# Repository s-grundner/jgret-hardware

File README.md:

# jgret-hardware

## Pico VGA Board

| Vorne                        | Hinten                             |
| ---------------------------- | ---------------------------------- |
|  |  |

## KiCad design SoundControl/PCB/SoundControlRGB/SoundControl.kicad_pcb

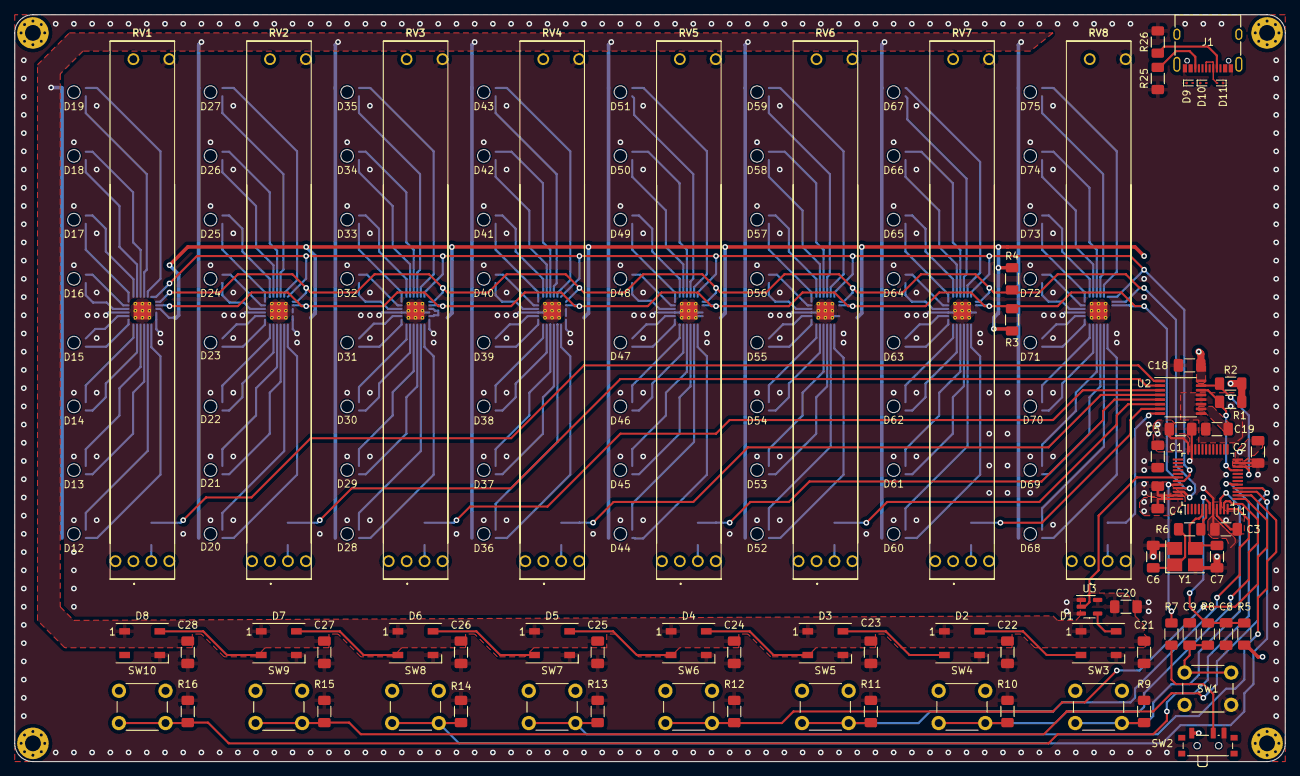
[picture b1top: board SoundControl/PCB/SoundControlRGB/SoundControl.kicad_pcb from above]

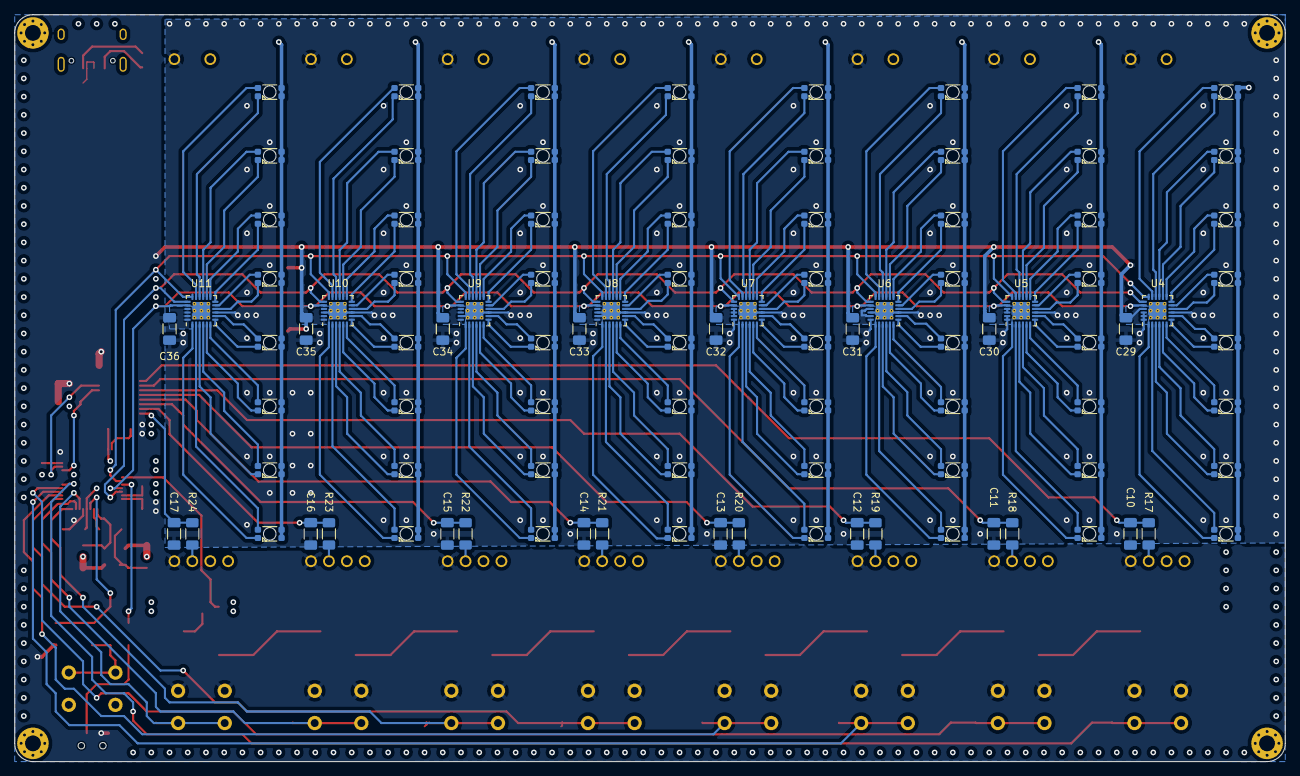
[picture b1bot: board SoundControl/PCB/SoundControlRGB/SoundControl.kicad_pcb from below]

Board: 4 copper layers, 177.2 x 104.1 mm, 168 parts (32 on the bottom side), 181 nets.

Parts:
C1, C8, C18: 2u2; C_1206_3216Metric_Pad1.33x1.80mm_HandSolder
C2, C3, C4, C5, C9, C19, C20, C21, C22, C23, C24, C25, C26, C27, C28: 100n; C_1206_3216Metric_Pad1.33x1.80mm_HandSolder
C6, C7: Dim; C_1206_3216Metric_Pad1.33x1.80mm_HandSolder
C10, C11, C12, C13, C14, C15, C16, C17: 56n; C_1206_3216Metric_Pad1.33x1.80mm_HandSolder
C29, C30, C31, C32, C33, C34, C35, C36: 1u; C_1206_3216Metric_Pad1.33x1.80mm_HandSolder
D1, D2, D3, D4, D5, D6, D7, D8: WS2812B; LED_WS2812B_PLCC4_5.0x5.0mm_P3.2mm
D9, D10, D11: ESD9B5.0ST5G; D_SOD-923
D12, D13, D14, D15, D16, D17, D18, D19, D20, D21, D22, D23, D24, D25, D26, D27, D28, D29, D30, D31, D32, D33, D34, D35, D36, D37, D38, D39, D40, D41, D42, D43, D44, D45, D46, D47, D48, D49, D50, D51, D52, D53, D54, D55, D56, D57, D58, D59, D60, D61, D62, D63, D64, D65, D66, D67, D68, D69, D70, D71, D72, D73, D74, D75: Wuerth_WL-SBRW
J1: USB_C_Receptacle_USB2.0; USB_C_Receptacle_XKB_U262-16XN-4BVC11
R1, R2, R3, R4: 3k3; R_1206_3216Metric_Pad1.30x1.75mm_HandSolder
R5, R9, R10, R11, R12, R13, R14, R15, R16: 10k; R_1206_3216Metric_Pad1.30x1.75mm_HandSolder
R6: Dim; R_1206_3216Metric_Pad1.30x1.75mm_HandSolder
R7, R8: 10R; R_1206_3216Metric_Pad1.30x1.75mm_HandSolder
R17, R18, R19, R20, R21, R22, R23, R24: 5k6; R_1206_3216Metric_Pad1.30x1.75mm_HandSolder
R25, R26: 1k; R_1206_3216Metric_Pad1.30x1.75mm_HandSolder
RV1, RV2, RV3, RV4, RV5, RV6, RV7, RV8: 10k; RS60112A600N
SW1, SW3, SW4, SW5, SW6, SW7, SW8, SW9, SW10: SW_Panasonic_EVQPUC; SW_PUSH_6mm
SW2: SW_SPDT; SW_SPDT_PCM12
U1: STM32F103C8Tx; LQFP-48_7x7mm_P0.5mm
U2: ADS7828; TSSOP-16_4.4x5mm_P0.65mm
U3: 74AHC1G125; SOT-23-5
U4, U5, U6, U7, U8, U9, U10, U11: LP3943; WQFN-24-1EP_4x4mm_P0.5mm_EP2.45x2.45mm_ThermalVias
Y1: Dim; Crystal_SMD_TXC_7M-4Pin_3.2x2.5mm_HandSoldering

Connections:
+3V3: C1.1, C2.1, C3.1, C4.1, C5.1, C18.1, C29.1, C30.1, C31.1, C32.1, C33.1, C34.1, C35.1, C36.1, R1.1, R2.1, R3.1, R4.1, R5.1, RV1.4, RV2.4, RV3.4, RV4.4, RV5.4, RV6.4, RV7.4, RV8.4, SW2.1 (A), SW3.1, SW4.1, SW5.1, SW6.1, SW7.1, SW8.1, SW9.1, SW10.1, U1.9 (VDDA), U1.24 (VDD), U1.36 (VDD), U1.48 (VDD), U2.16 (VDD), U4.21 (VDD), U5.21 (VDD), U5.22 (A0), U6.21 (VDD), U6.23 (A1), U7.21 (VDD), U7.22 (A0), U7.23 (A1), U8.21 (VDD), U8.24 (A2), U9.21 (VDD), U9.22 (A0), U9.24 (A2), U10.21 (VDD), U10.23 (A1), U10.24 (A2), U11.21 (VDD), U11.22 (A0), U11.23 (A1), U11.24 (A2)
+5V: C20.1, C21.1, C22.1, C23.1, C24.1, C25.1, C26.1, C27.1, C28.1, D1.1 (VDD), D2.1 (VDD), D3.1 (VDD), D4.1 (VDD), D5.1 (VDD), D6.1 (VDD), D7.1 (VDD), D8.1 (VDD), D9.2 (A2), D12.3 (A2), D12.4 (A1), D13.3 (A2), D13.4 (A1), D14.3 (A2), D14.4 (A1), D15.3 (A2), D15.4 (A1), D16.3 (A2), D16.4 (A1), D17.3 (A2), D17.4 (A1), D18.3 (A2), D18.4 (A1), D19.3 (A2), D19.4 (A1), D20.3 (A2), D20.4 (A1), D21.3 (A2), D21.4 (A1), D22.3 (A2), D22.4 (A1), D23.3 (A2), D23.4 (A1), D24.3 (A2), D24.4 (A1), D25.3 (A2), D25.4 (A1), D26.3 (A2), D26.4 (A1), D27.3 (A2), D27.4 (A1), D28.3 (A2), D28.4 (A1), D29.3 (A2), D29.4 (A1), D30.3 (A2), D30.4 (A1), D31.3 (A2), D31.4 (A1), D32.3 (A2), D32.4 (A1), D33.3 (A2), D33.4 (A1), D34.3 (A2), D34.4 (A1), D35.3 (A2), D35.4 (A1), D36.3 (A2), D36.4 (A1), D37.3 (A2), D37.4 (A1), D38.3 (A2), D38.4 (A1), D39.3 (A2), D39.4 (A1), D40.3 (A2), D40.4 (A1), D41.3 (A2), D41.4 (A1), D42.3 (A2), D42.4 (A1), D43.3 (A2), D43.4 (A1), D44.3 (A2), D44.4 (A1), D45.3 (A2), D45.4 (A1), D46.3 (A2), D46.4 (A1), D47.3 (A2), D47.4 (A1), D48.3 (A2), D48.4 (A1), D49.3 (A2), D49.4 (A1), D50.3 (A2), D50.4 (A1), D51.3 (A2), D51.4 (A1), D52.3 (A2), D52.4 (A1), D53.3 (A2), D53.4 (A1), D54.3 (A2), D54.4 (A1), D55.3 (A2), D55.4 (A1), D56.3 (A2), D56.4 (A1), D57.3 (A2), D57.4 (A1), D58.3 (A2), D58.4 (A1), D59.3 (A2), D59.4 (A1), D60.3 (A2), D60.4 (A1), D61.3 (A2), D61.4 (A1), D62.3 (A2), D62.4 (A1), D63.3 (A2), D63.4 (A1), D64.3 (A2), D64.4 (A1), D65.3 (A2), D65.4 (A1), D66.3 (A2), D66.4 (A1), D67.3 (A2), D67.4 (A1), D68.3 (A2), D68.4 (A1), D69.3 (A2), D69.4 (A1), D70.3 (A2), D70.4 (A1), D71.3 (A2), D71.4 (A1), D72.3 (A2), D72.4 (A1), D73.3 (A2), D73.4 (A1), D74.3 (A2), D74.4 (A1), D75.3 (A2), D75.4 (A1), J1.A4 (VBUS), J1.A9 (VBUS), J1.B4 (VBUS), J1.B9 (VBUS), U3.5 (VCC)
/8x Potentiometer and ADC/POT1: C10.1, R17.2, U2.1 (CH0)
/8x Potentiometer and ADC/POT2: C11.1, R18.2, U2.2 (CH1)
/8x Potentiometer and ADC/POT3: C12.1, R19.2, U2.3 (CH2)
/8x Potentiometer and ADC/POT4: C13.1, R20.2, U2.4 (CH3)
/8x Potentiometer and ADC/POT5: C14.1, R21.2, U2.5 (CH4)
/8x Potentiometer and ADC/POT6: C15.1, R22.2, U2.6 (CH5)
/8x Potentiometer and ADC/POT7: C16.1, R23.2, U2.7 (CH6)
/8x Potentiometer and ADC/POT8: C17.1, R24.2, U2.8 (CH7)
/CTRL_NRST: U1.43 (PB7), U4.18 (NRST), U5.18 (NRST), U6.18 (NRST), U7.18 (NRST), U8.18 (NRST), U9.18 (NRST), U10.18 (NRST), U11.18 (NRST)
/I2C1_SCL: R3.2, U1.45 (PB8), U4.20 (SCL), U5.20 (SCL), U6.20 (SCL), U7.20 (SCL), U8.20 (SCL), U9.20 (SCL), U10.20 (SCL), U11.20 (SCL)
/I2C1_SDA: R4.2, U1.46 (PB9), U4.19 (SCL), U5.19 (SCL), U6.19 (SCL), U7.19 (SCL), U8.19 (SCL), U9.19 (SCL), U10.19 (SCL), U11.19 (SCL)
/I2C2_SCL: R1.2, U1.21 (PB10), U2.14 (SCL)
/I2C2_SDA: R2.2, U1.22 (PB11), U2.15 (SDA)
/LED/LED1: D1.2 (DOUT), D2.4 (DIN)
/LED/LED2: D2.2 (DOUT), D3.4 (DIN)
/LED/LED3: D3.2 (DOUT), D4.4 (DIN)
/LED/LED4: D4.2 (DOUT), D5.4 (DIN)
/LED/LED5: D5.2 (DOUT), D6.4 (DIN)
/LED/LED6: D6.2 (DOUT), D7.4 (DIN)
/LED/LED7: D7.2 (DOUT), D8.4 (DIN)
/LED_DIN: U1.42 (PB6), U3.2
/RGB CONTROL/RBG_LEDS1/G1: D12.1 (K1), U4.1 (LED0)
/RGB CONTROL/RBG_LEDS1/G2: D13.1 (K1), U4.3 (LED2)
/RGB CONTROL/RBG_LEDS1/G3: D14.1 (K1), U4.5 (LED4)
/RGB CONTROL/RBG_LEDS1/G4: D15.1 (K1), U4.7 (LED6)
/RGB CONTROL/RBG_LEDS1/G5: D16.1 (K1), U4.10 (LED8)
/RGB CONTROL/RBG_LEDS1/G6: D17.1 (K1), U4.12 (LED10)
/RGB CONTROL/RBG_LEDS1/G7: D18.1 (K1), U4.14 (LED12)
/RGB CONTROL/RBG_LEDS1/G8: D19.1 (K1), U4.16 (LED14)
/RGB CONTROL/RBG_LEDS1/R1: D12.2 (K2), U4.2 (LED1)
/RGB CONTROL/RBG_LEDS1/R2: D13.2 (K2), U4.4 (LED3)
/RGB CONTROL/RBG_LEDS1/R3: D14.2 (K2), U4.6 (LED5)
/RGB CONTROL/RBG_LEDS1/R4: D15.2 (K2), U4.8 (LED7)
/RGB CONTROL/RBG_LEDS1/R5: D16.2 (K2), U4.11 (LED9)
/RGB CONTROL/RBG_LEDS1/R6: D17.2 (K2), U4.13 (LED11)
/RGB CONTROL/RBG_LEDS1/R7: D18.2 (K2), U4.15 (LED13)
/RGB CONTROL/RBG_LEDS1/R8: D19.2 (K2), U4.17 (LED16)
/RGB CONTROL/RBG_LEDS2/G1: D20.1 (K1), U5.1 (LED0)
/RGB CONTROL/RBG_LEDS2/G2: D21.1 (K1), U5.3 (LED2)
/RGB CONTROL/RBG_LEDS2/G3: D22.1 (K1), U5.5 (LED4)
/RGB CONTROL/RBG_LEDS2/G4: D23.1 (K1), U5.7 (LED6)
/RGB CONTROL/RBG_LEDS2/G5: D24.1 (K1), U5.10 (LED8)
/RGB CONTROL/RBG_LEDS2/G6: D25.1 (K1), U5.12 (LED10)
/RGB CONTROL/RBG_LEDS2/G7: D26.1 (K1), U5.14 (LED12)
/RGB CONTROL/RBG_LEDS2/G8: D27.1 (K1), U5.16 (LED14)
/RGB CONTROL/RBG_LEDS2/R1: D20.2 (K2), U5.2 (LED1)
/RGB CONTROL/RBG_LEDS2/R2: D21.2 (K2), U5.4 (LED3)
/RGB CONTROL/RBG_LEDS2/R3: D22.2 (K2), U5.6 (LED5)
/RGB CONTROL/RBG_LEDS2/R4: D23.2 (K2), U5.8 (LED7)
/RGB CONTROL/RBG_LEDS2/R5: D24.2 (K2), U5.11 (LED9)
/RGB CONTROL/RBG_LEDS2/R6: D25.2 (K2), U5.13 (LED11)
/RGB CONTROL/RBG_LEDS2/R7: D26.2 (K2), U5.15 (LED13)
/RGB CONTROL/RBG_LEDS2/R8: D27.2 (K2), U5.17 (LED16)
/RGB CONTROL/RBG_LEDS3/G1: D28.1 (K1), U6.1 (LED0)
/RGB CONTROL/RBG_LEDS3/G2: D29.1 (K1), U6.3 (LED2)
/RGB CONTROL/RBG_LEDS3/G3: D30.1 (K1), U6.5 (LED4)
/RGB CONTROL/RBG_LEDS3/G4: D31.1 (K1), U6.7 (LED6)
/RGB CONTROL/RBG_LEDS3/G5: D32.1 (K1), U6.10 (LED8)
/RGB CONTROL/RBG_LEDS3/G6: D33.1 (K1), U6.12 (LED10)
/RGB CONTROL/RBG_LEDS3/G7: D34.1 (K1), U6.14 (LED12)
/RGB CONTROL/RBG_LEDS3/G8: D35.1 (K1), U6.16 (LED14)
/RGB CONTROL/RBG_LEDS3/R1: D28.2 (K2), U6.2 (LED1)
/RGB CONTROL/RBG_LEDS3/R2: D29.2 (K2), U6.4 (LED3)
/RGB CONTROL/RBG_LEDS3/R3: D30.2 (K2), U6.6 (LED5)
/RGB CONTROL/RBG_LEDS3/R4: D31.2 (K2), U6.8 (LED7)
/RGB CONTROL/RBG_LEDS3/R5: D32.2 (K2), U6.11 (LED9)
/RGB CONTROL/RBG_LEDS3/R6: D33.2 (K2), U6.13 (LED11)
/RGB CONTROL/RBG_LEDS3/R7: D34.2 (K2), U6.15 (LED13)
/RGB CONTROL/RBG_LEDS3/R8: D35.2 (K2), U6.17 (LED16)
/RGB CONTROL/RBG_LEDS4/G1: D36.1 (K1), U7.1 (LED0)
/RGB CONTROL/RBG_LEDS4/G2: D37.1 (K1), U7.3 (LED2)
/RGB CONTROL/RBG_LEDS4/G3: D38.1 (K1), U7.5 (LED4)
/RGB CONTROL/RBG_LEDS4/G4: D39.1 (K1), U7.7 (LED6)
/RGB CONTROL/RBG_LEDS4/G5: D40.1 (K1), U7.10 (LED8)
/RGB CONTROL/RBG_LEDS4/G6: D41.1 (K1), U7.12 (LED10)
/RGB CONTROL/RBG_LEDS4/G7: D42.1 (K1), U7.14 (LED12)
/RGB CONTROL/RBG_LEDS4/G8: D43.1 (K1), U7.16 (LED14)
/RGB CONTROL/RBG_LEDS4/R1: D36.2 (K2), U7.2 (LED1)
/RGB CONTROL/RBG_LEDS4/R2: D37.2 (K2), U7.4 (LED3)
/RGB CONTROL/RBG_LEDS4/R3: D38.2 (K2), U7.6 (LED5)
/RGB CONTROL/RBG_LEDS4/R4: D39.2 (K2), U7.8 (LED7)
/RGB CONTROL/RBG_LEDS4/R5: D40.2 (K2), U7.11 (LED9)
/RGB CONTROL/RBG_LEDS4/R6: D41.2 (K2), U7.13 (LED11)
/RGB CONTROL/RBG_LEDS4/R7: D42.2 (K2), U7.15 (LED13)
/RGB CONTROL/RBG_LEDS4/R8: D43.2 (K2), U7.17 (LED16)
/RGB CONTROL/RBG_LEDS5/G1: D52.1 (K1), U9.1 (LED0)
/RGB CONTROL/RBG_LEDS5/G2: D53.1 (K1), U9.3 (LED2)
/RGB CONTROL/RBG_LEDS5/G3: D54.1 (K1), U9.5 (LED4)
/RGB CONTROL/RBG_LEDS5/G4: D55.1 (K1), U9.7 (LED6)
/RGB CONTROL/RBG_LEDS5/G5: D56.1 (K1), U9.10 (LED8)
/RGB CONTROL/RBG_LEDS5/G6: D57.1 (K1), U9.12 (LED10)
/RGB CONTROL/RBG_LEDS5/G7: D58.1 (K1), U9.14 (LED12)
/RGB CONTROL/RBG_LEDS5/G8: D59.1 (K1), U9.16 (LED14)
/RGB CONTROL/RBG_LEDS5/R1: D52.2 (K2), U9.2 (LED1)
/RGB CONTROL/RBG_LEDS5/R2: D53.2 (K2), U9.4 (LED3)
/RGB CONTROL/RBG_LEDS5/R3: D54.2 (K2), U9.6 (LED5)
/RGB CONTROL/RBG_LEDS5/R4: D55.2 (K2), U9.8 (LED7)
/RGB CONTROL/RBG_LEDS5/R5: D56.2 (K2), U9.11 (LED9)
/RGB CONTROL/RBG_LEDS5/R6: D57.2 (K2), U9.13 (LED11)
/RGB CONTROL/RBG_LEDS5/R7: D58.2 (K2), U9.15 (LED13)
/RGB CONTROL/RBG_LEDS5/R8: D59.2 (K2), U9.17 (LED16)
/RGB CONTROL/RBG_LEDS6/G1: D68.1 (K1), U11.1 (LED0)
/RGB CONTROL/RBG_LEDS6/G2: D69.1 (K1), U11.3 (LED2)
/RGB CONTROL/RBG_LEDS6/G3: D70.1 (K1), U11.5 (LED4)
/RGB CONTROL/RBG_LEDS6/G4: D71.1 (K1), U11.7 (LED6)
/RGB CONTROL/RBG_LEDS6/G5: D72.1 (K1), U11.10 (LED8)
/RGB CONTROL/RBG_LEDS6/G6: D73.1 (K1), U11.12 (LED10)
/RGB CONTROL/RBG_LEDS6/G7: D74.1 (K1), U11.14 (LED12)
/RGB CONTROL/RBG_LEDS6/G8: D75.1 (K1), U11.16 (LED14)
/RGB CONTROL/RBG_LEDS6/R1: D68.2 (K2), U11.2 (LED1)
/RGB CONTROL/RBG_LEDS6/R2: D69.2 (K2), U11.4 (LED3)
/RGB CONTROL/RBG_LEDS6/R3: D70.2 (K2), U11.6 (LED5)
/RGB CONTROL/RBG_LEDS6/R4: D71.2 (K2), U11.8 (LED7)
/RGB CONTROL/RBG_LEDS6/R5: D72.2 (K2), U11.11 (LED9)
/RGB CONTROL/RBG_LEDS6/R6: D73.2 (K2), U11.13 (LED11)
/RGB CONTROL/RBG_LEDS6/R7: D74.2 (K2), U11.15 (LED13)
/RGB CONTROL/RBG_LEDS6/R8: D75.2 (K2), U11.17 (LED16)
/RGB CONTROL/RBG_LEDS7/G1: D60.1 (K1), U10.1 (LED0)
/RGB CONTROL/RBG_LEDS7/G2: D61.1 (K1), U10.3 (LED2)
/RGB CONTROL/RBG_LEDS7/G3: D62.1 (K1), U10.5 (LED4)
/RGB CONTROL/RBG_LEDS7/G4: D63.1 (K1), U10.7 (LED6)
/RGB CONTROL/RBG_LEDS7/G5: D64.1 (K1), U10.10 (LED8)
/RGB CONTROL/RBG_LEDS7/G6: D65.1 (K1), U10.12 (LED10)
/RGB CONTROL/RBG_LEDS7/G7: D66.1 (K1), U10.14 (LED12)
/RGB CONTROL/RBG_LEDS7/G8: D67.1 (K1), U10.16 (LED14)
/RGB CONTROL/RBG_LEDS7/R1: D60.2 (K2), U10.2 (LED1)
/RGB CONTROL/RBG_LEDS7/R2: D61.2 (K2), U10.4 (LED3)
/RGB CONTROL/RBG_LEDS7/R3: D62.2 (K2), U10.6 (LED5)
/RGB CONTROL/RBG_LEDS7/R4: D63.2 (K2), U10.8 (LED7)
/RGB CONTROL/RBG_LEDS7/R5: D64.2 (K2), U10.11 (LED9)
/RGB CONTROL/RBG_LEDS7/R6: D65.2 (K2), U10.13 (LED11)
/RGB CONTROL/RBG_LEDS7/R7: D66.2 (K2), U10.15 (LED13)
/RGB CONTROL/RBG_LEDS7/R8: D67.2 (K2), U10.17 (LED16)
/RGB CONTROL/RBG_LEDS8/G1: D44.1 (K1), U8.1 (LED0)
/RGB CONTROL/RBG_LEDS8/G2: D45.1 (K1), U8.3 (LED2)
/RGB CONTROL/RBG_LEDS8/G3: D46.1 (K1), U8.5 (LED4)
/RGB CONTROL/RBG_LEDS8/G4: D47.1 (K1), U8.7 (LED6)
/RGB CONTROL/RBG_LEDS8/G5: D48.1 (K1), U8.10 (LED8)
/RGB CONTROL/RBG_LEDS8/G6: D49.1 (K1), U8.12 (LED10)
/RGB CONTROL/RBG_LEDS8/G7: D50.1 (K1), U8.14 (LED12)
/RGB CONTROL/RBG_LEDS8/G8: D51.1 (K1), U8.16 (LED14)
/RGB CONTROL/RBG_LEDS8/R1: D44.2 (K2), U8.2 (LED1)
/RGB CONTROL/RBG_LEDS8/R2: D45.2 (K2), U8.4 (LED3)
/RGB CONTROL/RBG_LEDS8/R3: D46.2 (K2), U8.6 (LED5)
/RGB CONTROL/RBG_LEDS8/R4: D47.2 (K2), U8.8 (LED7)
/RGB CONTROL/RBG_LEDS8/R5: D48.2 (K2), U8.11 (LED9)
/RGB CONTROL/RBG_LEDS8/R6: D49.2 (K2), U8.13 (LED11)
/RGB CONTROL/RBG_LEDS8/R7: D50.2 (K2), U8.15 (LED13)
/RGB CONTROL/RBG_LEDS8/R8: D51.2 (K2), U8.17 (LED16)
/SW1: R9.1, SW3.2, U1.10 (PA0)
/SW2: R10.1, SW4.2, U1.11 (PA1)
/SW3: R11.1, SW5.2, U1.12 (PA2)
/SW4: R12.1, SW6.2, U1.13 (PA3)
/SW5: R13.1, SW7.2, U1.14 (PA4)
/SW6: R14.1, SW8.2, U1.15 (PA5)
/SW7: R15.1, SW9.2, U1.16 (PA6)
/SW8: R16.1, SW10.2, U1.17 (PA7)
/Strapping/BOOT0: R7.2, U1.44 (BOOT0)
/Strapping/NRST: C8.1, R5.2, R8.1, U1.7 (NRST)
/Strapping/XTAL_IN: C7.1, U1.5 (PD0), Y1.3
/Strapping/XTAL_OUT: R6.2, U1.6 (PD1)
/USB_DN: D11.2 (A2), J1.A7 (D-), J1.B7 (D-), U1.33 (PA12)
/USB_DP: D10.2 (A2), J1.A6 (D+), J1.B6 (D+), U1.32 (PA11)
GND: C1.2, C2.2, C3.2, C4.2, C5.2, C6.2, C7.2, C8.2, C9.2, C10.2, C11.2, C12.2, C13.2, C14.2, C15.2, C16.2, C17.2, C18.2, C19.2, C20.2, C21.2, C22.2, C23.2, C24.2, C25.2, C26.2, C27.2, C28.2, C29.2, C30.2, C31.2, C32.2, C33.2, C34.2, C35.2, C36.2, D1.3 (VSS), D2.3 (VSS), D3.3 (VSS), D4.3 (VSS), D5.3 (VSS), D6.3 (VSS), D7.3 (VSS), D8.3 (VSS), D9.1 (A1), D10.1 (A1), D11.1 (A1), J1.A1 (GND), J1.A12 (GND), J1.B1 (GND), J1.B12 (GND), R9.2, R10.2, R11.2, R12.2, R13.2, R14.2, R15.2, R16.2, R25.2, R26.2, RV1.6, RV2.6, RV3.6, RV4.6, RV5.6, RV6.6, RV7.6, RV8.6, SW1.1, SW2.3 (C), U1.8 (VSSA), U1.23 (VSS), U1.35 (VSS), U1.47 (VSS), U2.9 (GND), U2.11 (COM), U2.12 (A0), U2.13 (A1), U3.1, U3.3 (GND), U4.9 (GND), U4.22 (A0), U4.23 (A1), U4.24 (A2), U4.25 (GND), U5.9 (GND), U5.23 (A1), U5.24 (A2), U5.25 (GND), U6.9 (GND), U6.22 (A0), U6.24 (A2), U6.25 (GND), U7.9 (GND), U7.24 (A2), U7.25 (GND), U8.9 (GND), U8.22 (A0), U8.23 (A1), U8.25 (GND), U9.9 (GND), U9.23 (A1), U9.25 (GND), U10.9 (GND), U10.22 (A0), U10.25 (GND), U11.9 (GND), U11.25 (GND), Y1.2, Y1.4
unnamed: C6.1, R6.1, Y1.1
unnamed: C9.1, R8.2, SW1.2
unnamed: D1.4 (DIN), U3.4
unnamed: J1.A5 (CC1), R26.1
unnamed: J1.B5 (CC2), R25.1
unnamed: R17.1, RV1.5
unnamed: R18.1, RV2.5
unnamed: R19.1, RV3.5
unnamed: R20.1, RV4.5
unnamed: R21.1, RV5.5
unnamed: R22.1, RV6.5
unnamed: R23.1, RV7.5
unnamed: R24.1, RV8.5
unnamed: R7.1, SW2.2 (B)
unnamed: C19.1, U2.10 (REF)

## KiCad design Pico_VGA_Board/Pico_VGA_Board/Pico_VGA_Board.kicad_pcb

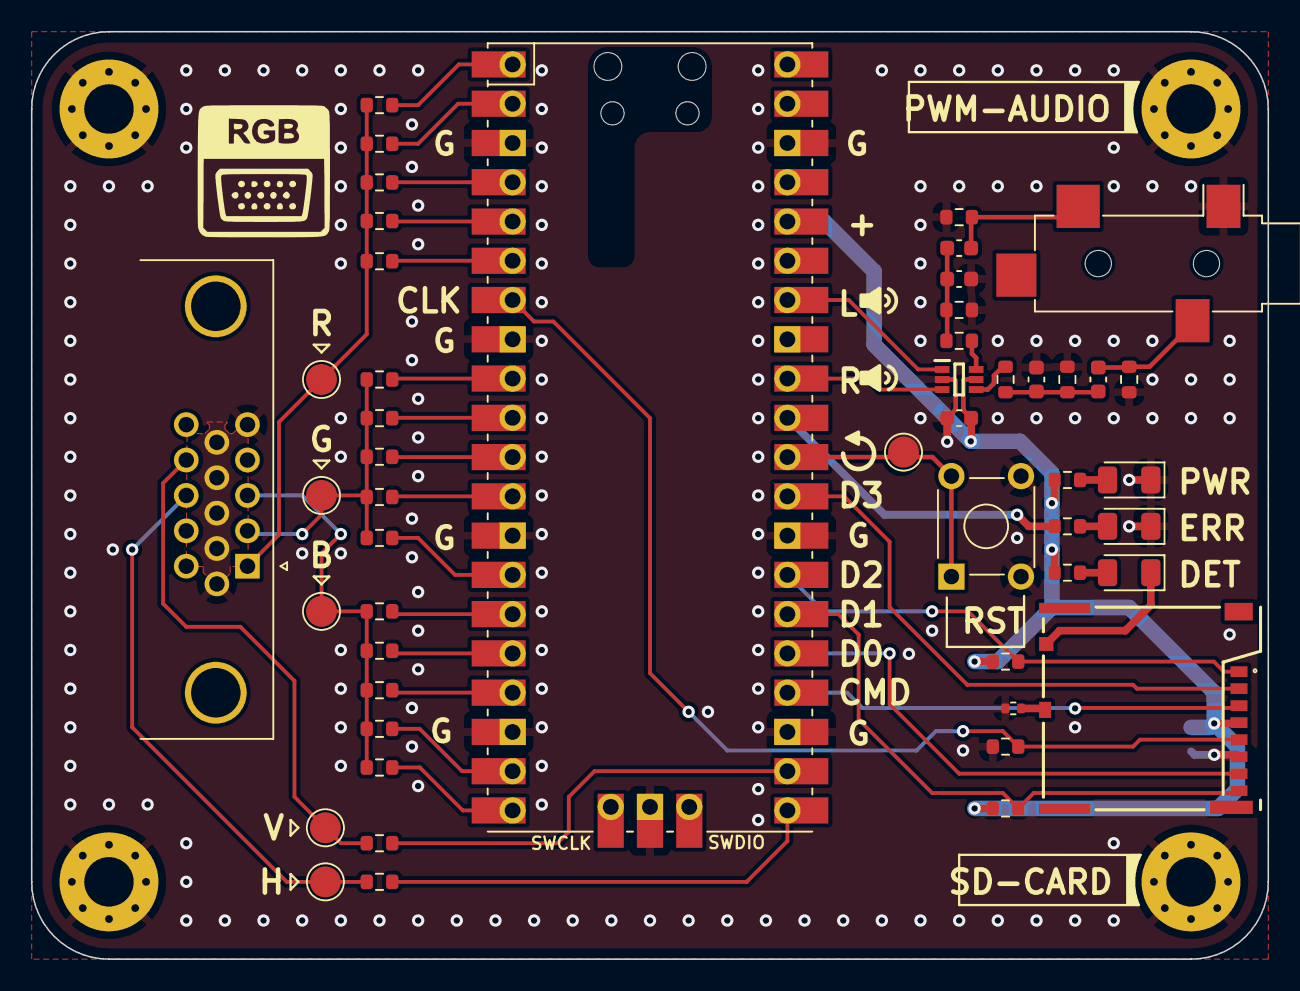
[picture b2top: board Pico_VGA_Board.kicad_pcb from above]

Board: 2 copper layers, 80.0 x 60.0 mm, 55 parts (1 on the bottom side), 45 nets.

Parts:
C1: 10u; C_0603_1608Metric
C2, C3, C5: 100n; C_0603_1608Metric
C4, C6: 47u; C_0603_1608Metric
D1, D2, D3: LED; LED_1206_3216Metric
H1, H2, H3, H4: MountingHole_Pad; MountingHole_3.2mm_M3_Pad_Via
IC1: NC7WZ17P6X; SOP65P210X110-6N
J1: DE15_Plug_HighDensity; DSUB-15-HD_Female_Horizontal_P2.29x1.98mm_EdgePinOffset3.03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
J2: Micro_SD_Card_Det1; 503398-1892
J3: AudioJack3; Jack_3.5mm_CUI_SJ-3524-SMT_Horizontal
R1, R6, R11: 499; R_0603_1608Metric
R2, R7, R12: 1k; R_0603_1608Metric
R3, R8, R13: 2k; R_0603_1608Metric
R4, R9, R14: 4.02k; R_0603_1608Metric
R5, R10, R15: 8.06k; R_0603_1608Metric
R16, R17: 47; R_0603_1608Metric
R18, R19: 10k; R_0603_1608Metric
R20: n.b.; R_0603_1608Metric
R21, R23, R30: Dim; R_0603_1608Metric
R22: R_Smol; R_0402_1005Metric
R24: 220R; R_0603_1608Metric
R25: 220; R_0603_1608Metric
R26: 100R; R_0603_1608Metric
R27: 100; R_0603_1608Metric
R28, R29: 1.8k; R_0603_1608Metric
SW1: SW_MEC_5E; SW_TH_Tactile_Omron_B3F-10xx
TP1, TP2, TP3, TP4, TP5, TP11: TestPoint; TestPoint_Pad_D2.0mm
U1: Pico; RPi_Pico_SMD_TH

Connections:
+3V3: C1.1, C2.1, IC1.5 (VCC), J2.4 (VDD), R18.1, R19.1, R21.1, R23.2, U1.36 (3V3)
/GPIO0: R5.1, U1.1 (GPIO0)
/GPIO1: R4.1, U1.2 (GPIO1)
/GPIO2: R3.1, U1.4 (GPIO2)
/GPIO3: R2.1, U1.5 (GPIO3)
/GPIO4: R1.1, U1.6 (GPIO4)
/GPIO6: R10.1, U1.9 (GPIO6)
/GPIO7: R9.1, U1.10 (GPIO7)
/GPIO8: R8.1, U1.11 (GPIO8)
/GPIO9: R7.1, U1.12 (GPIO9)
/GPIO10: R6.1, U1.14 (GPIO10)
/GPIO11: R15.1, U1.15 (GPIO11)
/GPIO12: R14.1, U1.16 (GPIO12)
/GPIO13: R13.1, U1.17 (GPIO13)
/GPIO14: R12.1, U1.19 (GPIO14)
/GPIO15: R11.1, U1.20 (GPIO15)
/GPIO27: IC1.3 (A2), U1.32 (GPIO27_ADC1)
/GPIO28: IC1.1 (A1), U1.34 (GPIO28_ADC2)
/HSYNC: J1.13, R16.2, TP4.1
/SD_CLK: J2.5 (CLK), R20.1, U1.7 (GPIO5)
/SD_CMD: J2.3 (CMD), U1.24 (GPIO18)
/SD_DAT0: J2.7 (DAT0), U1.25 (GPIO19)
/SD_DAT1: J2.8 (DAT1), R19.2, U1.26 (GPIO20)
/SD_DAT2: J2.1 (DAT2), R18.2, U1.27 (GPIO21)
/SD_DAT3: J2.2 (DAT3/CD), U1.29 (GPIO22)
/SD_ERR_LED: R30.1, U1.31 (GPIO26_ADC0)
/VGA_B: J1.3, R11.2, R12.2, R13.2, R14.2, R15.2, TP3.1
/VGA_G: J1.2, R6.2, R7.2, R8.2, R9.2, R10.2, TP2.1
/VGA_R: J1.1, R1.2, R2.2, R3.2, R4.2, R5.2, TP1.1
/VSYNC: J1.14, R17.2, TP5.1
GND: C1.2, C2.2, C3.2, C5.2, D2.1 (K), D3.1 (K), H1.1, H2.1, H3.1, H4.1, IC1.2 (GND), J1.5, J1.6, J1.7, J1.8, J1.9, J1.10, J2.6 (VSS), J3.S, R20.2, R22.1, R26.1, R27.1, R28.1, R29.1, SW1.2, U1.3 (GND), U1.8 (GND), U1.13 (GND), U1.18 (GND), U1.23 (GND), U1.28 (GND), U1.38 (GND), U1.42 (GND)
unnamed: C3.1, C4.1, R25.2, R27.2
unnamed: C4.2, J3.R, R28.2
unnamed: C5.1, C6.1, R24.2, R26.2
unnamed: C6.2, J3.T, R29.2
unnamed: D1.2 (A), R21.2
unnamed: D1.1 (K), J2.9 (DET)
unnamed: D2.2 (A), R23.1
unnamed: D3.2 (A), R30.2
unnamed: IC1.6 (Y1), R24.1
unnamed: IC1.4 (Y2), R25.1
unnamed: J2.10 (SHIELD), R22.2
unnamed: R16.1, U1.21 (GPIO16)
unnamed: R17.1, U1.22 (GPIO17)
unnamed: SW1.1, TP11.1, U1.30 (RUN)

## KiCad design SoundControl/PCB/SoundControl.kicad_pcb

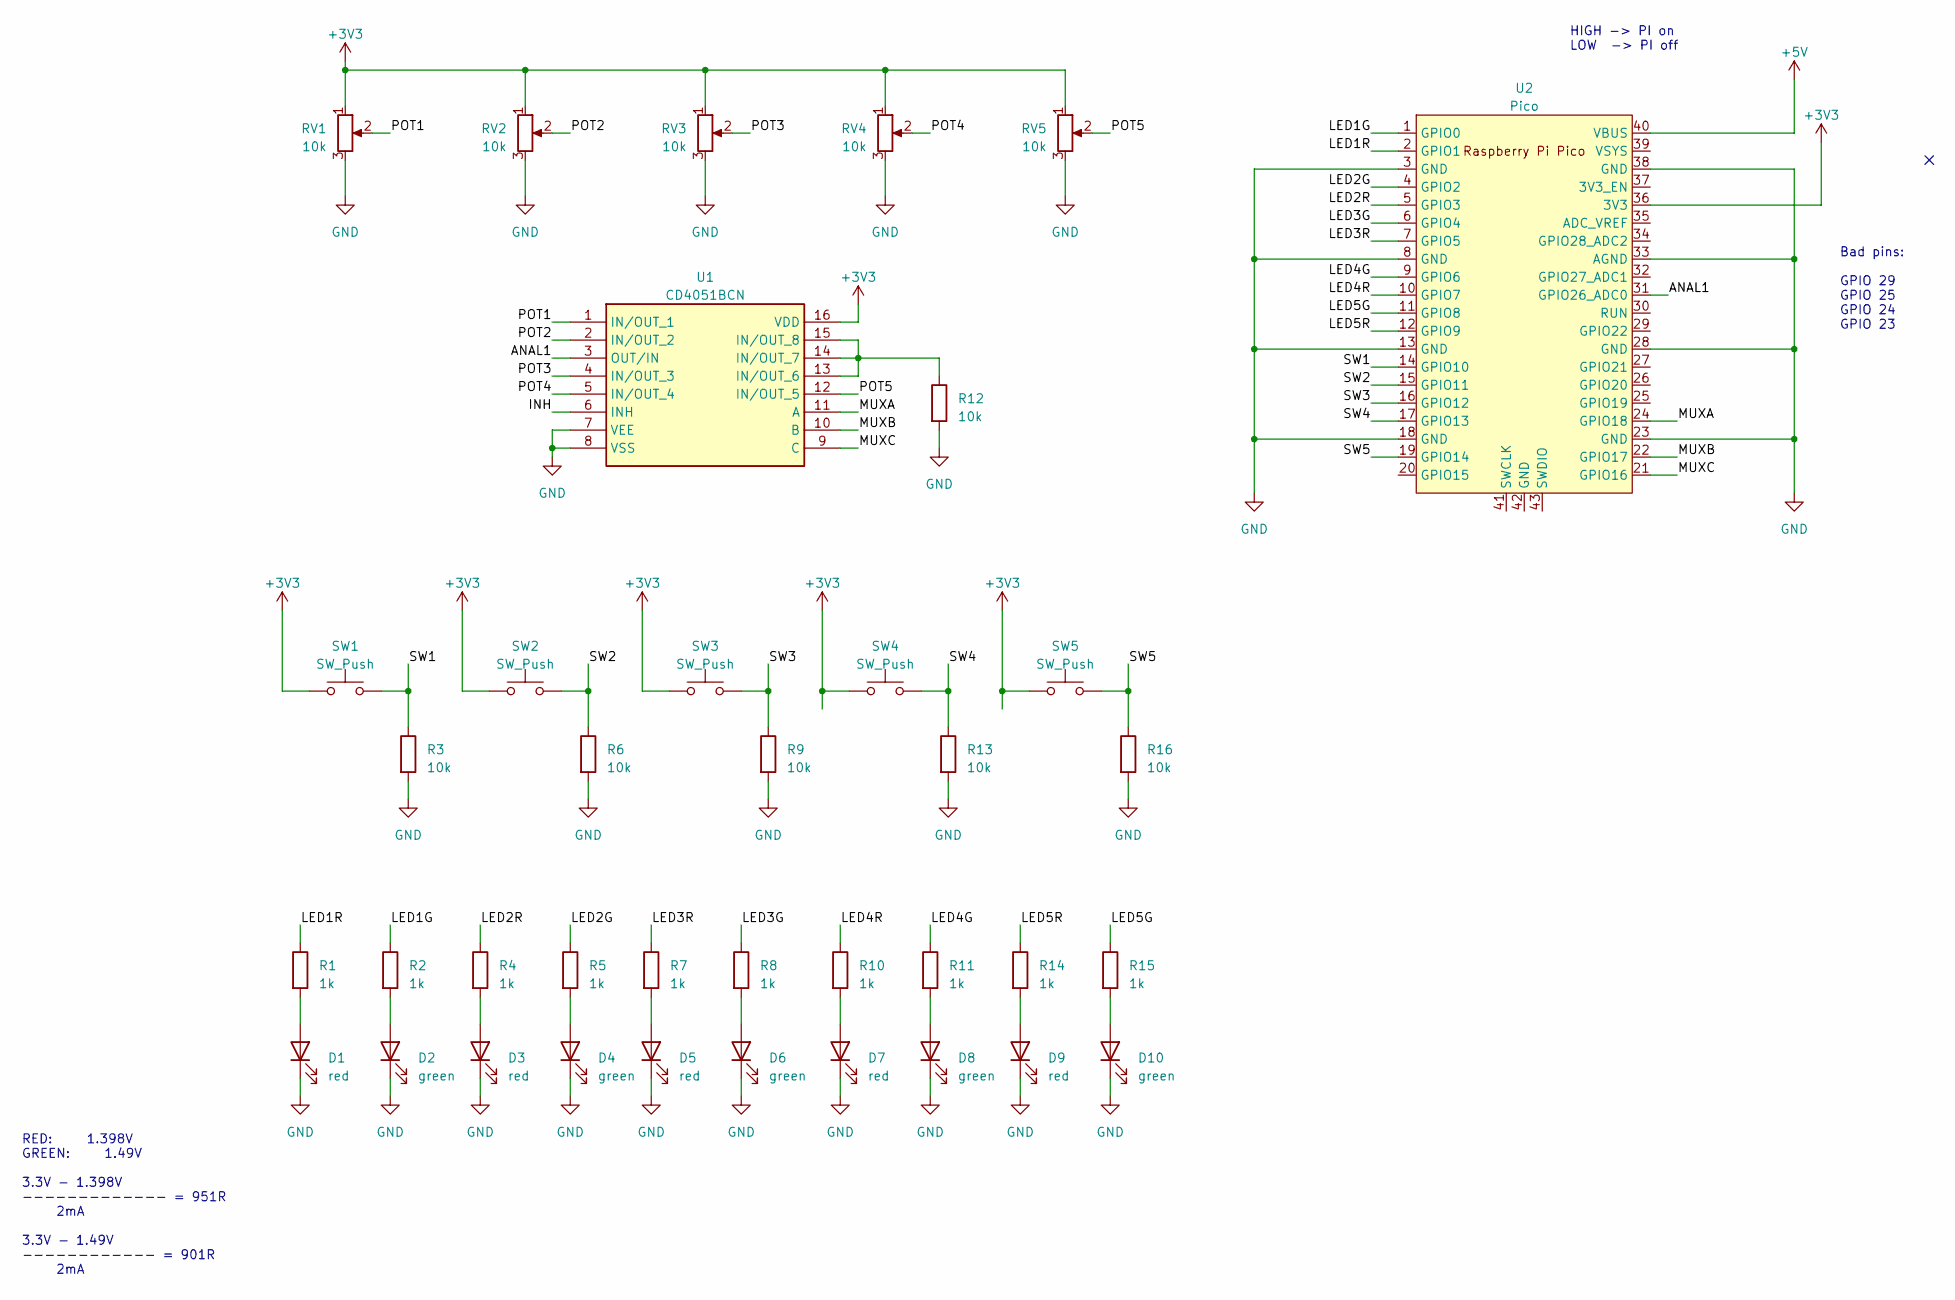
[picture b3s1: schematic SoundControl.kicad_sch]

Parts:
D1, D3, D5, D7, D9: red; LED_D5.0mm
D2, D4, D6, D8, D10: green; LED_D5.0mm
R1, R2, R4, R5, R7, R8, R10, R11, R14, R15: 1k; R_Axial_DIN0207_L6.3mm_D2.5mm_P15.24mm_Horizontal
R3, R6, R9, R12, R13, R16: 10k; R_Axial_DIN0207_L6.3mm_D2.5mm_P10.16mm_Horizontal
RV1, RV2, RV3, RV4, RV5: 10k; RS60112A600N
SW1, SW2, SW3, SW4, SW5: SW_Push; SW_PUSH_6mm
U1: CD4051BCN; DIP787W58P254L1930H508Q16N; Manufacturer_Part_Number CD4051BCN
U2: Pico; RPi_Pico_THT

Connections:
+3V3: RV1.1, RV2.1, RV3.1, RV4.1, RV5.1, SW1.1, SW2.1, SW3.1, SW4.1, SW5.1, U1.16 (VDD), U2.36 (3V3)
+5V: U2.40 (VBUS)
/ANAL1: U1.3 (OUT/IN), U2.31 (GPIO26_ADC0)
/INH: U1.6 (INH)
/LED1G: R2.1, U2.1 (GPIO0)
/LED1R: R1.1, U2.2 (GPIO1)
/LED2G: R5.1, U2.4 (GPIO2)
/LED2R: R4.1, U2.5 (GPIO3)
/LED3G: R8.1, U2.6 (GPIO4)
/LED3R: R7.1, U2.7 (GPIO5)
/LED4G: R11.1, U2.9 (GPIO6)
/LED4R: R10.1, U2.10 (GPIO7)
/LED5G: R15.1, U2.11 (GPIO8)
/LED5R: R14.1, U2.12 (GPIO9)
/MUXA: U1.11 (A), U2.24 (GPIO18)
/MUXB: U1.10 (B), U2.22 (GPIO17)
/MUXC: U1.9 (C), U2.21 (GPIO16)
/POT1: RV1.2, U1.1 (IN/OUT_1)
/POT2: RV2.2, U1.2 (IN/OUT_2)
/POT3: RV3.2, U1.4 (IN/OUT_3)
/POT4: RV4.2, U1.5 (IN/OUT_4)
/POT5: RV5.2, U1.12 (IN/OUT_5)
/SW1: R3.1, SW1.2, U2.14 (GPIO10)
/SW2: R6.1, SW2.2, U2.15 (GPIO11)
/SW3: R9.1, SW3.2, U2.16 (GPIO12)
/SW4: R13.1, SW4.2, U2.17 (GPIO13)
/SW5: R16.1, SW5.2, U2.19 (GPIO14)
GND: D1.1 (K), D2.1 (K), D3.1 (K), D4.1 (K), D5.1 (K), D6.1 (K), D7.1 (K), D8.1 (K), D9.1 (K), D10.1 (K), R3.2, R6.2, R9.2, R12.2, R13.2, R16.2, RV1.3, RV2.3, RV3.3, RV4.3, RV5.3, U1.7 (VEE), U1.8 (VSS), U2.3 (GND), U2.8 (GND), U2.13 (GND), U2.18 (GND), U2.23 (GND), U2.28 (GND), U2.33 (AGND), U2.38 (GND)
unnamed: D1.2 (A), R1.2
unnamed: D2.2 (A), R2.2
unnamed: D3.2 (A), R4.2
unnamed: D4.2 (A), R5.2
unnamed: D5.2 (A), R7.2
unnamed: D6.2 (A), R8.2
unnamed: D7.2 (A), R10.2
unnamed: D8.2 (A), R11.2
unnamed: D9.2 (A), R14.2
unnamed: D10.2 (A), R15.2
unnamed: R12.1, U1.13 (IN/OUT_6), U1.14 (IN/OUT_7), U1.15 (IN/OUT_8)

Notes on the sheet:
Bad pins: GPIO 29 GPIO 25 GPIO 24 GPIO 23
RED: 1.398V GREEN: 1.49V 3.3V - 1.398V ------------- = 951R 2mA 3.3V - 1.49V ------------ = 901R 2mA
HIGH -> PI on LOW -> PI off

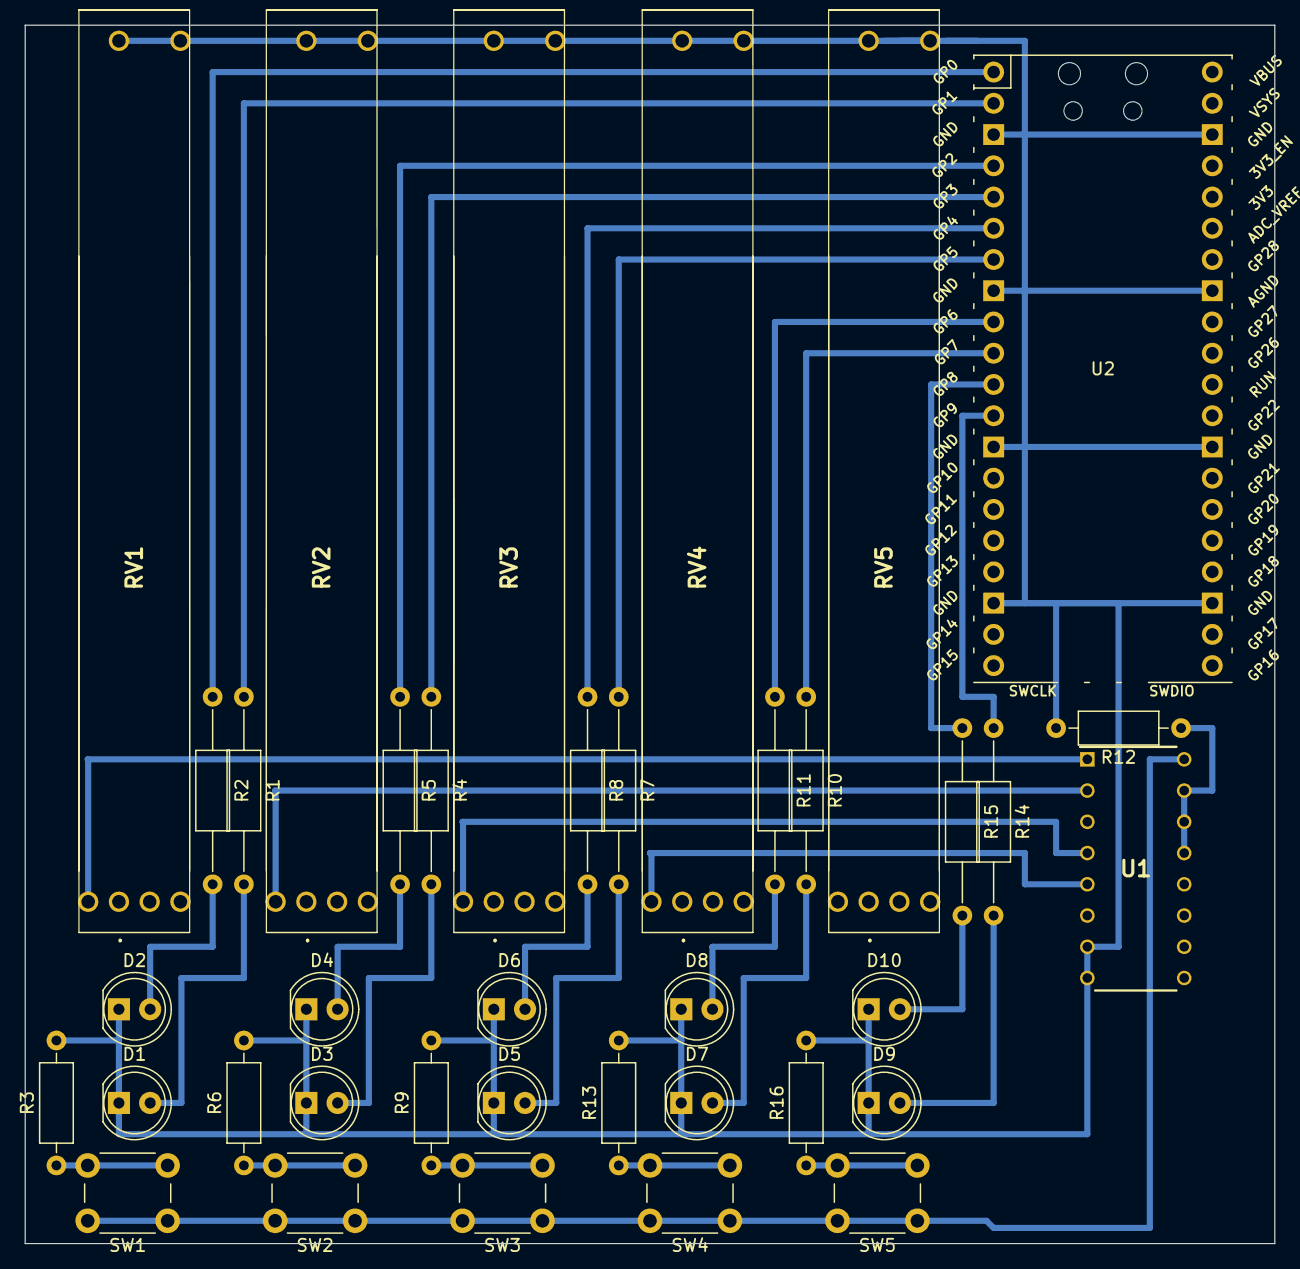
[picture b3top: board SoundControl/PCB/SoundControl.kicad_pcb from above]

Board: 2 copper layers, 101.6 x 99.1 mm, 38 parts (0 on the bottom side), 37 nets.

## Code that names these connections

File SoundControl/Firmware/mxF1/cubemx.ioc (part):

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Mcu.Name=STM32F103C(8-B)Tx
Mcu.Package=LQFP48
Mcu.UserName=STM32F103C8Tx
PA0-WKUP.Signal=GPIO_Input
PA1.Signal=GPIO_Input
PA10.Mode=Asynchronous
PA10.Signal=USART1_RX
PA11.Mode=Device
PA11.Signal=USB_DM
PA12.Mode=Device
PA12.Signal=USB_DP
PA13.Mode=Serial_Wire
PA13.Signal=SYS_JTMS-SWDIO
PA14.Mode=Serial_Wire
PA14.Signal=SYS_JTCK-SWCLK
PA2.Signal=GPIO_Input
PA3.Signal=GPIO_Input
PA4.Signal=GPIO_Input
PA5.Signal=GPIO_Input
PA6.Signal=GPIO_Input
PA7.Signal=GPIO_Input
PA9.Mode=Asynchronous
PA9.Signal=USART1_TX
PB10.Mode=I2C
PB10.Signal=I2C2_SCL
PB11.Mode=I2C
PB11.Signal=I2C2_SDA
PB6.Signal=S_TIM4_CH1
PB7.Signal=S_TIM4_CH2
PB8.Mode=I2C
PB8.Signal=I2C1_SCL
PB9.Mode=I2C
PB9.Signal=I2C1_SDA
PD0-OSC_IN.Mode=HSE-External-Oscillator
PD0-OSC_IN.Signal=RCC_OSC_IN
PD1-OSC_OUT.Mode=HSE-External-Oscillator
PD1-OSC_OUT.Signal=RCC_OSC_OUT
RCC.SYSCLKFreq_VALUE=48000000
RCC.SYSCLKSource=RCC_SYSCLKSOURCE_PLLCLK
board=custom

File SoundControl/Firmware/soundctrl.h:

#ifndef SOUNDCTRL_H_
#define SOUNDCTRL_H_

#define PIN_LED1R 0
#define PIN_LED1G 1
#define PIN_LED2R 2
#define PIN_LED2G 3
#define PIN_LED3R 4
#define PIN_LED3G 5
#define PIN_LED4R 6
#define PIN_LED4G 7
#define PIN_LED5R 8
#define PIN_LED5G 9

#define PIN_SW1 10
#define PIN_SW2 11
#define PIN_SW3 12
#define PIN_SW4 13
#define PIN_SW5 14

#define PIN_MUXA 18
#define PIN_MUXB 17
#define PIN_MUXC 16

#define PIN_ANAL1 26
#define ADC_IN 0 // GPIO 26

void init_hw();

#endif

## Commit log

2023-08-11 init
2023-08-11 added gitignore
2023-08-11 added gitignore & cleanup
2023-08-20 UPD Board
2023-08-21 Added a büdl
2023-08-21 Beeren an da Rückseitn pflanzt
2023-08-21 Stitching DK
2023-08-21 neiche büdln
2023-08-21 Büdl
2023-08-21 Silkscreen Pins
2023-08-21 1-Heiten
2023-08-21 upd Silkscreen
2024-02-27 added SoundControl
2024-02-29 firmware and pinout
2025-01-23 Sound Control 2 Versions
